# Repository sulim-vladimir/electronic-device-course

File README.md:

# Метеостанція на ESP8266

Невелика метеостанція з живленням від акумулятора: вона вимірює температуру і тиск повітря, надсилає дані на сервер і в Telegram, а між вимірюваннями спить, щоб акумулятор тримав якомога довше.

- **Мозок:** модуль ESP-12F (ESP8266) з Wi-Fi.
- **Датчики:** DS18B20 (температура) і BMP280 (тиск і температура).
- **Живлення:** акумулятор 18650 із захистом (DW01 + FS8205) і стабілізатором 3,3 В.
- **Сон:** ESP прокидається раз на 10 хвилин, вимірює, надсилає і знову засинає.

Мета — перетворити цей прототип на продукт: друковані плати, які виготовляє і збирає завод JLCPCB, корпус для вулиці, а потім невелика серія на продаж. Шлях до цього розписаний у курсі в цьому репозиторії.

## Як це виглядає зараз

Це поточна версія v2, ще до змін, які ти зробиш на курсі (наприклад, на ній є замикання, яке ти знайдеш на кроці 09).

| Плата зверху | Схема |
|---|---|
|  |  |

Повна схема — у [`pcb/last-version.kicad_sch`](pcb/last-version.kicad_sch) (відкривай через `pcb/last-version.kicad_pro` у KiCad). Пояснення кожного блоку — на сторінці «Схема v2» в курсі.

## Що де лежить

| Папка / файл | Що там |
|---|---|
| [`index.html`](index.html) | Курс: 26 кроків від схеми до зібраних плат. Відкривається в браузері, працює без інтернету. |
| [`pcb/`](pcb/) | Проєкт KiCad: схема і плата (`last-version.kicad_pro`). |
| [`firmware/`](firmware/) | Прошивка для Arduino IDE (`projectcpcs_v2/projectcpcs_v2.ino`). |
| [`submissions/`](submissions/) | Твої відповіді: по одному файлу на кожен крок курсу, вже підготовлені. |
| `practice/` | Тут буде твоя тренувальна плата (з'явиться на кроці «Тренувальна плата»). |
| [`tools/`](tools/) | Допоміжний скрипт для курсу. |
| [`MENTOR.md`](MENTOR.md) | Інструкція для наставника. |
| [`images/`](images/) | Зображення для цього README. |

## Перші кроки

1. **Прийми запрошення до репозиторію.** Наставник додасть тебе як учасника (collaborator). GitHub надішле лист, або запрошення буде на github.com у сповіщеннях (Notifications).
2. **Встанови git**, якщо його ще немає: [git-scm.com/downloads](https://git-scm.com/downloads). Перевір у терміналі: `git --version`.
3. **Завантаж (clone) репозиторій** — так у тебе одразу буде справжня копія, з якою ти працюватимеш увесь курс. Найпростіше через VS Code: **View → Command Palette** (`Ctrl`+`Shift`+`P`) → **Git: Clone** → встав адресу нижче → вибери папку. Коли VS Code попросить увійти в GitHub, погодься: він відкриє браузер. Або в терміналі:
   ```
   git clone https://github.com/sulim-vladimir/electronic-device-course.git
   cd electronic-device-course
   ```
   Звичайний пароль GitHub у терміналі не спрацює: потрібен вхід через VS Code або personal access token.
4. **Відкрий курс.** У папці репозиторію двічі клацни `index.html` — він відкриється в браузері.
   
5. **Почни з кроку 00** «Як працює цей курс». На кроці 02 ти навчишся робити коміти, гілки і pull request і надішлеш свою першу роботу на перевірку.
6. **Застряг?** Спершу підказки в самому кроці, потім «Схема v2» і словник English → Українська (у меню курсу ліворуч). Якщо не допомогло — запитай наставника в Telegram: який крок, що пробував, і скріншот.

## Що є в курсі

| | |
|---|---|
| **Кожен крок:** мета, навіщо це, завдання по порядку.  | **Поради і підказки:** поради інженера, а підказки відкриваються по одній, коли застряг.  |
| **Типові проблеми:** що означає кожна помилка DRC і що з нею робити.  | **Здати на перевірку:** що заповнити і готові команди git для pull request.  |
| **Схема v2:** кожен блок схеми — що він робить і чому.  | **Словник:** англійські терміни з KiCad, даташитів і GitHub з перекладом.  |

## Як проходить кожен крок

1. Почни з актуального `main` і створи гілку для кроку:
   ```
   git switch main
   git pull
   git switch -c step-06
   ```
2. Виконай завдання зі сторінки курсу.
3. Заповни `submissions/step-06.md`. Скріншоти клади в `submissions/img/`.
4. Зроби коміт і push:
   ```
   git status
   git add -A
   git commit -m "Крок 06: Як працює глибокий сон"
   git push -u origin step-06
   ```
5. На GitHub відкрий **pull request** із `step-06` у `main` з такою самою назвою, як коміт.
6. Наставник перевіряє:
   - **Approved і merged:** крок прийнято. Виконай `git switch main` і `git pull`, потім починай наступний крок.
   - **Changes requested:** прочитай коментарі, виправ, зроби коміт і push у ту саму гілку. Pull request оновиться сам.

**По одному кроку.** Файли KiCad погано зливаються, тому наступний крок починай лише після того, як попередній злито.

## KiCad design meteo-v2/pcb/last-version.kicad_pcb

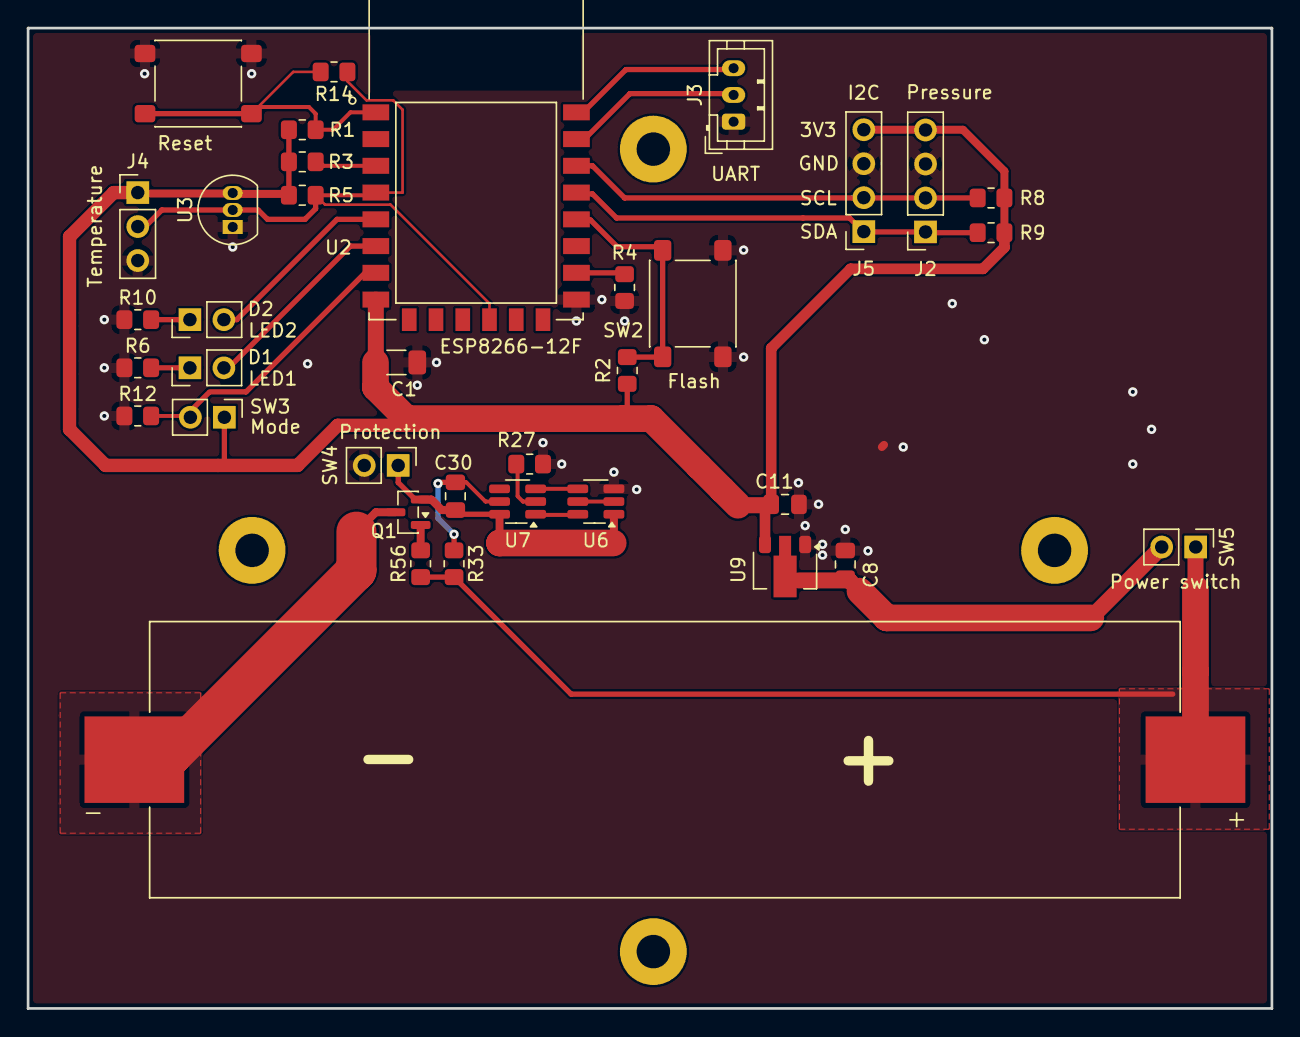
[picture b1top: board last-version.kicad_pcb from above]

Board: 2 copper layers, 93.0 x 73.3 mm, 40 parts (0 on the bottom side), 27 nets.

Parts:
BT2: 1042; BAT_1042
C1: 100uF; C_1206_3216Metric_Pad1.33x1.80mm_HandSolder
C8, C11: 1u; C_0805_2012Metric_Pad1.18x1.45mm_HandSolder
C30: 100n; C_0805_2012Metric_Pad1.18x1.45mm_HandSolder
D1: LED1; PinHeader_1x02_P2.54mm_Vertical
D2: LED2; PinHeader_1x02_P2.54mm_Vertical
H1, H2, H3, H4: MountingHole; MountingHole_2.5mm_Pad
J2: Pressure; PinSocket_1x04_P2.54mm_Vertical
J3: UART; JST_PH_B3B-PH-K_1x03_P2.00mm_Vertical
J4: Temperature; PinHeader_1x03_P2.54mm_Vertical
J5: I2C; PinSocket_1x04_P2.54mm_Vertical
Q1: AO3400A; SOT-23
R1, R2, R3, R4, R5, R6, R8, R9, R10, R12, R56: 10k; R_0805_2012Metric_Pad1.20x1.40mm_HandSolder
R14, R27: 1k; R_0805_2012Metric_Pad1.20x1.40mm_HandSolder
R33: 100R; R_0805_2012Metric_Pad1.20x1.40mm_HandSolder
SW1: Reset; SW_SPST_PTS645Sx43SMTR92
SW2: Flash; SW_SPST_PTS645Sx43SMTR92
SW3: Mode; PinHeader_1x02_P2.54mm_Vertical
SW4: Protection; PinHeader_1x02_P2.54mm_Vertical
SW5: Power switch; PinHeader_1x02_P2.54mm_Vertical
U2: ESP8266-12F; XCVR_ESP8266-12E_ESP-12E
U3: DS18B20; TO-92_Inline
U6: FS8205; SOT-23-6_Handsoldering
U7: DW01; SOT-23-6_Handsoldering
U9: HT7333-A; SOT-89-3

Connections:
3V3: C1.1, C11.1, J2.4, J4.1, J5.4, R1.1, R2.2, R3.2, R5.1, R8.1, R9.1, SW3.1, U2.8 (VCC), U3.3 (V_{DD}), U9.3 (VO)
B+: BT2.P, R33.2, R56.1, SW5.1 (A)
GND: C1.2, C8.2, C11.2, J2.3, J3.1, J4.3, J5.3, R4.2, R6.1, R10.1, R12.1, R27.1, SW1.1, SW2.2, SW4.2, U2.15 (GND), U3.1 (GND), U6.3 (S2), U9.1 (GND)
LED1: D2.2 (A), U2.5 (IO14)
LED2: D1.2 (A), U2.6 (IO12)
Mode: R12.2, SW3.2, U2.7 (IO13)
unnamed: D1.1 (K), R6.2
unnamed: D2.1 (K), R10.2
unnamed: BT2.N, Q1.3 (D)
unnamed: Q1.1 (G), R56.2
unnamed: C30.1, Q1.2 (S), SW4.1, U6.1 (S1), U7.6 (GND)
unnamed: R3.1, U2.3 (EN)
unnamed: R2.1, SW2.1, U2.18 (IO0)
unnamed: R4.1, U2.16 (IO15)
unnamed: R14.1, U2.4 (IO16)
unnamed: R1.2, R14.2, SW1.2, U2.1 (RESET)
unnamed: U6.2 (D12), U6.5 (D12)
unnamed: U6.6 (G1), U7.1 (OD)
unnamed: U6.4 (G2), U7.3 (OC)
unnamed: R27.2, U7.2 (CS)
unnamed: C30.2, R33.1, U7.5 (VCC)
OneWire: J4.2, R5.2, U2.12 (IO10), U3.2 (DQ)
RX: J3.3, U2.22 (TXD)
SCL: J2.2, J5.2, R8.2, U2.20 (IO5)
SDA: J2.1, J5.1, R9.2, U2.19 (IO4)
TX: J3.2, U2.21 (RXD)
VBAT: C8.1, SW5.2 (B), U9.2 (VI)

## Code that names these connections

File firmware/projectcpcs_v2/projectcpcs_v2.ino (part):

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//
// Pins on this board:
//   GPIO4  SDA, GPIO5 SCL      BMP280 (J2 / J5)
//   GPIO10 OneWire             DS18B20 (U3 / J4). Set Flash Mode to DIO or DOUT,
//                              in QIO mode GPIO10 belongs to the flash chip.
//   GPIO12 LED2, GPIO14 LED1
//   GPIO13 Mode jumper (SW3)   closed = config portal; R12 pulls it low when open
//   GPIO16                     wired to RESET through R14 for deep-sleep wake.
//                              Do not use it in code.
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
